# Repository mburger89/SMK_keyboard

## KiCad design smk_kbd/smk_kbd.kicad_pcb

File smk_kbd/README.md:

# Gateron LP 5×12 Wireless Keyboard — KiCad Project

59-key (5×12, bottom row 5 + 2U + 5) hot-swap low-profile keyboard, ESP32-C6 wireless, Li-ion powered with USB-C charging and a hard power switch.

Open `smk_kbd.kicad_pro` in KiCad 9. Files are in KiCad 8 format, which KiCad 9 opens natively (it will save them forward in v9 format). All symbols and footprints are embedded **and** provided as project-local libraries (`kbd.pretty`, `kbd.kicad_sym`) so nothing external is required.

## Layout

- 19.05 mm pitch, rows 0–3 are full 12-key rows.
- Row 4: 5 keys (cols 0–4) + one **2U key** centered over the two middle 1U positions (electrically column 5) + 5 keys (cols 7–11). Column 6 has no switch in row 4.
- The 2U key uses the Gateron **plate-mounted** 2U stabilizer (KS-57B210T) — it clips to the plate, so the PCB needs no stabilizer holes. Keep the area around the 2U key clear of tall components (it already is).
- Board outline 234.5 × 116.5 mm; 6 × M2 mounting holes placed in the gaps between keys.

## Switch / socket footprint

Built from the Gateron datasheets you provided:

- ø5.2 mm center hole (stem post), 2 × ø3.0 mm contact barrels at (−4.4, 4.7) and (+2.6, 5.75) from switch center, 2.55 mm square solder pads on the **back** copper — sockets mount on the back, switches insert from the front.
- Verified against the KS-2P02B01-02 drawing (7.0 mm pin spread, 1.05 mm vertical offset, 14×14 body).

## Electrical design

**Matrix** — COL2ROW: `COL → switch → diode anode → cathode → ROW`. One 1N4148W (SOD-123, back side) per key, placed left of each switch.

**GPIO map (ESP32-C6-MINI-1)**

| Function | GPIO | Module pin |
|---|---|---|
| ROW0–ROW3 (inputs) | IO0–IO3 | 12, 13, 5, 6 |
| ROW4 (input) | IO5 | 10 |
| COL0–COL11 (outputs) | IO6, IO7, IO8, IO14, IO15, IO18–IO23, IO17 | 15, 16, 22, 19, 20, 24–29, 30 |
| VBAT sense (÷2) | IO4 / ADC1_CH4 | 9 |
| USB D− / D+ | IO12 / IO13 | 17 / 18 |
| BOOT button | IO9 | 23 |
| RESET button | EN | 8 |
| Spare / UART log | TXD0 (IO16) | 31 (unconnected) |

Rows are on IO0–IO3 + IO5 deliberately: these are **LP (low-power) GPIOs**, so the firmware can use them for deep-sleep key-press wakeup, and all are ADC-capable. Note IO4/IO5/IO8/IO9/IO15 are strapping pins — harmless for a matrix (inputs at boot), just don't hold keys during reset if flashing misbehaves.

**Power**

- USB-C (HRO TYPE-C-31-M-12, 16-pin USB 2.0) with 5.1 kΩ CC pulldowns → works with C-to-C cables. ESD protection via USBLC6-2SC6.
- Charger: MCP73831-2 with 2.0 kΩ PROG = **500 mA** charge current. Use a 1000 mAh+ Li-ion cell, or raise R3 to 10 kΩ for 100 mA with smaller cells. Charge LED on STAT.
- Power path (Feather-style): VBUS → Schottky (B5819W) → VSYS; battery → DMG3415U P-FET → VSYS. When USB is plugged in, the FET gate is pulled high and the board runs from USB while the battery charges; otherwise the FET conducts from the battery.
- **Charging works with the power switch OFF** — the charger connects to the battery ahead of the switch.
- ON/OFF: the side-actuated slide switch (MSK-12C02) sits flush with the rear board edge — its lever pokes out through a case cutout next to USB. It drives the AP2112K-3.3 LDO **EN** pin between VSYS and GND — it switches microamps, not the load current, and gives a true off state (LDO Iq ≈ 55 µA off the battery when on; ~0 when off).
- Battery voltage divider 1 MΩ/1 MΩ + 100 nF into IO4 for fuel-gauge readings.
- Battery connector: JST-SH 2-pin (SM02B-SRSS-TB), surface-mount on the **back** of the board, only ~1.6 mm tall, cable exits toward the board interior. Batteries usually ship with JST-PH plugs — order one with an SH plug or re-terminate. **Check polarity against the + mark before plugging in.**

## Routing — DONE

The board is **fully routed**: matrix (columns on F.Cu, rows on B.Cu, one via
per key), MCU fanout, USB differential pair, charger, power path, LDO and
buttons — 570 track segments, 130 vias, 29 GND stitching vias. An independent
geometric check verified 0.2 mm copper clearance, 0.3 mm hole clearance,
0.3 mm edge clearance and single-component connectivity for every net.
`board_render.png` shows the routed board (red = front, blue = back).

GND is carried by the two full-board pours — fill them before export (the
export script does this automatically).

## Sending to PCBWay

1. `cd` into this folder and run the export script with KiCad's bundled Python
   (it fills the zones, saves, and writes `smk_kbd_gerbers.zip`):

   macOS: `/Applications/KiCad/KiCad.app/Contents/Frameworks/Python.framework/Versions/Current/bin/python3 export_fab.py`

   (Alternative: open the PCB in KiCad, press `B`, run DRC, then
   File → Fabrication Outputs → Gerbers + Drill Files and zip the output.)

2. Upload `smk_kbd_gerbers.zip` at pcbway.com → *Quick Order PCB*.

3. Order parameters:

   | Setting | Value |
   |---|---|
   | Board size | 234.5 × 116.5 mm |
   | Layers | 2 |
   | Thickness | **1.6 mm** |
   | Min track/spacing | 6/6 mil (design uses ≥ 0.2 mm — relaxed) |
   | Min hole | 0.3 mm |
   | Surface finish | HASL lead-free (or ENIG for nicer hot-swap pads) |
   | Copper | 1 oz |
   | Solder mask / silk | your choice |
   | Panelization | single piece |

4. Sanity checks before paying: view the Gerbers in PCBWay's online viewer or
   `gerbview` — confirm the GND pours are present on both layers (if they're
   missing you exported without filling zones) and the board outline is closed.

## PCB placement (why it routes easily)

- Socket pads are on the back; the **front layer is completely free under the matrix** — run columns vertically on F.Cu (each socket's COL pad is at the same x in a column; drop one via per key).
- Diodes are on the back, cathodes facing up — run rows horizontally on B.Cu. Row 4's 2U key is pre-assigned to column 5, so its column trace just jogs half a pitch.
- The diode anode pad sits 0.3 mm from its socket pad on the same net — join them with a stub trace.
- MCU/power strip along the top edge: battery + power mux + LDO left of the module, USB + ESD + charger right of it, BOOT/RESET buttons on the BACK of the board beside the module (press through case holes). Antenna points off the top edge with a built-in copper keepout zone (both layers) — don't route under it and keep the case plastic there.
- GND zones are defined on both layers — press `B` in pcbnew to fill.

## BOM (besides 59 switches, 59 sockets, keycaps, 2U plate stab)

| Ref | Part | Package |
|---|---|---|
| U1 | ESP32-C6-MINI-1 | SMD module |
| U2 | MCP73831-2ACI/OT | SOT-23-5 |
| U3 | AP2112K-3.3TRG1 | SOT-23-5 |
| U4 | USBLC6-2SC6 | SOT-23-6 |
| Q1 | DMG3415U (P-MOSFET) | SOT-23 |
| D1–D59 | 1N4148W | SOD-123 |
| D60 | B5819W / SS14 Schottky | SOD-123 |
| LED1 | LED (charge) | 0603 |
| J1 | HRO TYPE-C-31-M-12 (LCSC C165948) | SMD |
| J2 | JST SH **SM02B-SRSS-TB** (1.0 mm, low-profile side entry, on the **back**) | SMD |
| SW60/61 | 6×6 mm tactile (mounted on the **back** side) | THT |
| SW62 | MSK-12C02 side-actuated slide SPDT, lever exits rear edge | SMD |
| R1,R2 | 5.1 kΩ | 0603 |
| R3 | 2.0 kΩ | 0603 |
| R4 | 1 kΩ | 0603 |
| R5 | 100 kΩ | 0603 |
| R6,R7 | 1 MΩ | 0603 |
| R8 | 10 kΩ | 0603 |
| C1,C2 | 4.7 µF | 0603 |
| C3,C6 | 1 µF | 0603 |
| C4,C7 | 10 µF | 0603 |
| C5,C8 | 100 nF | 0603 |

## 3D models

Every footprint carries a 3D model, so KiCad's 3D viewer (`Alt+3`) shows the
assembled board:

- Switches: your `Gateron_KS-33.step` (in `3dmodels/`), one per key, plus a
  generated hot-swap socket model on the back side.
- ESP32-C6-MINI-1 and the MSK-12C02 slide switch: generated models in
  `3dmodels/` (dimensionally correct simplified shapes).
- Everything else (SOT-23s, 0603 R/C/LED, SOD-123 diodes, HRO USB-C, JST-PH,
  6 mm buttons) references KiCad 9's stock library via `${KICAD9_3DMODEL_DIR}`.
  If a part renders blank, install the "3D models" package from the KiCad
  installer — the references resolve automatically.

If the switch model appears rotated (LED window on the wrong side), edit one
footprint's model rotation and use Edit → "Change Footprints" to apply to all.

## Firmware notes

ZMK (with the ESP32 port) or ESP-IDF/Arduino work; the C6 supports BLE 5 + 802.15.4. Matrix: COL2ROW, diode direction col→row. Native USB (IO12/13) gives flashing and serial with no UART bridge; hold BOOT while tapping RESET for download mode.

## Final checks before ordering

1. Run `export_fab.py` (fills zones + saves), or open the PCB, press `B`, save.
2. Run KiCad's own DRC once for confidence — the design was verified by an independent geometric checker, but a second opinion is free.
3. Verify the slide-switch footprint against the exact part you buy (MSK-12C02 clones vary slightly).
4. The HRO USB-C legs are officially specced for thinner boards — they solder fine on 1.6 mm (standard practice on keyboards), or swap in a GCT USB4105 footprint if you prefer.

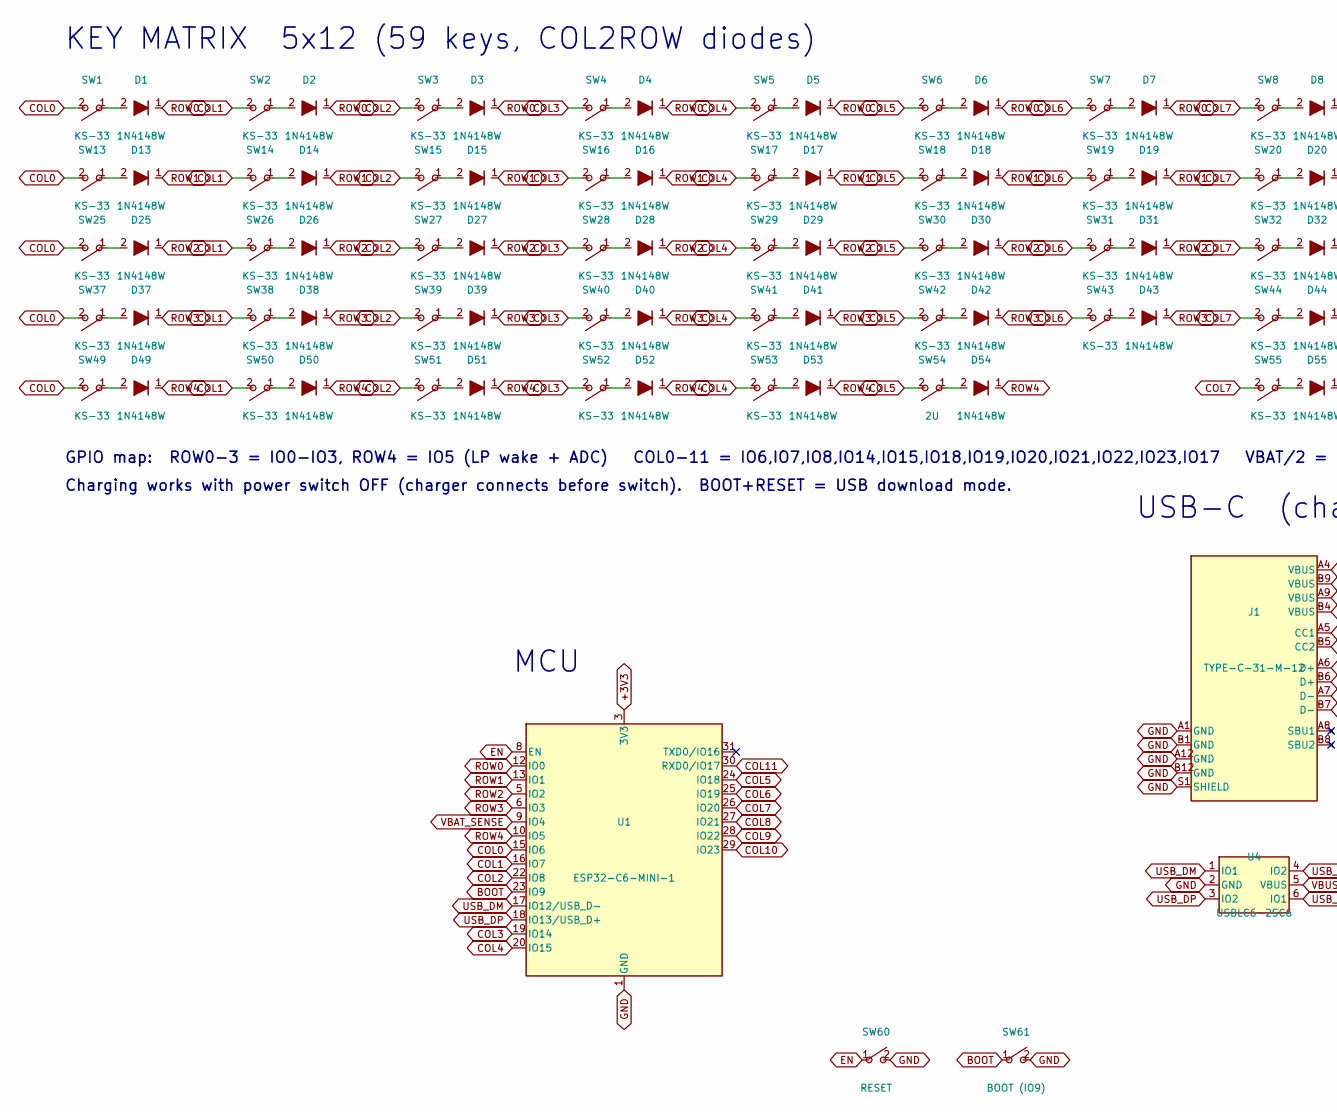
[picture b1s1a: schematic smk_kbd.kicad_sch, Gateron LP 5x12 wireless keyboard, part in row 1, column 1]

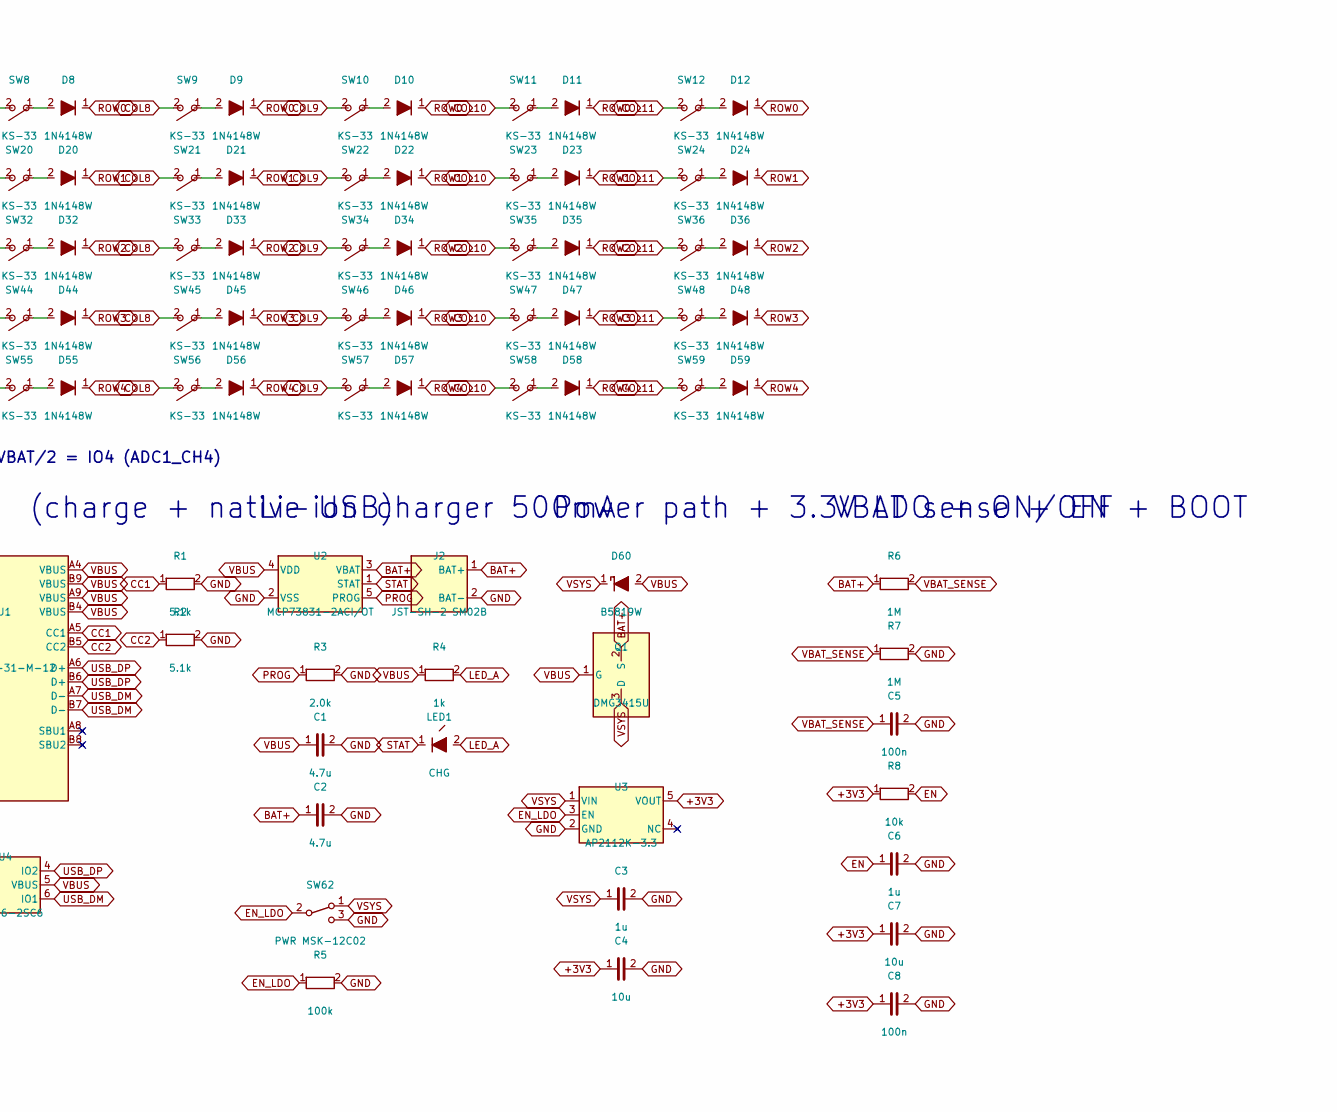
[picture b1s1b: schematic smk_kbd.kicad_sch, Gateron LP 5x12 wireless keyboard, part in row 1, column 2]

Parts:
C1, C2: 4.7u; RC_0603
C3, C6: 1u; RC_0603
C4, C7: 10u; RC_0603
C5, C8: 100n; RC_0603
D1, D2, D3, D4, D5, D6, D7, D8, D9, D10, D11, D12, D13, D14, D15, D16, D17, D18, D19, D20, D21, D22, D23, D24, D25, D26, D27, D28, D29, D30, D31, D32, D33, D34, D35, D36, D37, D38, D39, D40, D41, D42, D43, D44, D45, D46, D47, D48, D49, D50, D51, D52, D53, D54, D55, D56, D57, D58, D59: 1N4148W; D_SOD-123_Back
D60: B5819W; D_SOD-123_Back
J1: TYPE-C-31-M-12; USB_C_Receptacle_HRO_TYPE-C-31-M-12
J2: JST-SH-2 SM02B; JST_SH_SM02B_2pin_Back
LED1: CHG; LED_0603
Q1: DMG3415U; SOT-23
R1, R2: 5.1k; RC_0603
R3: 2.0k; RC_0603
R4: 1k; RC_0603
R5: 100k; RC_0603
R6, R7: 1M; RC_0603
R8: 10k; RC_0603
SW1, SW2, SW3, SW4, SW5, SW6, SW7, SW8, SW9, SW10, SW11, SW12, SW13, SW14, SW15, SW16, SW17, SW18, SW19, SW20, SW21, SW22, SW23, SW24, SW25, SW26, SW27, SW28, SW29, SW30, SW31, SW32, SW33, SW34, SW35, SW36, SW37, SW38, SW39, SW40, SW41, SW42, SW43, SW44, SW45, SW46, SW47, SW48, SW49, SW50, SW51, SW52, SW53, SW55, SW56, SW57, SW58, SW59: KS-33; SW_Gateron_KS33_HS
SW54: 2U; SW_Gateron_KS33_HS
SW60: RESET; SW_PUSH_6mm_THT
SW61: BOOT (IO9); SW_PUSH_6mm_THT
SW62: PWR MSK-12C02; SW_Slide_MSK12C02
U1: ESP32-C6-MINI-1
U2: MCP73831-2ACI/OT; SOT-23-5
U3: AP2112K-3.3; SOT-23-5
U4: USBLC6-2SC6; SOT-23-6

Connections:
+3V3: C4.1, C7.1, C8.1, R8.1, U1.3 (3V3), U3.5 (VOUT)
BAT+: C2.1, J2.1 (BAT+), Q1.2 (S), R6.1, U2.3 (VBAT)
BOOT: SW61.1, U1.23 (IO9)
CC1: J1.A5 (CC1), R1.1
CC2: J1.B5 (CC2), R2.1
COL0: SW1.2, SW13.2, SW25.2, SW37.2, SW49.2, U1.15 (IO6)
COL1: SW2.2, SW14.2, SW26.2, SW38.2, SW50.2, U1.16 (IO7)
COL2: SW3.2, SW15.2, SW27.2, SW39.2, SW51.2, U1.22 (IO8)
COL3: SW4.2, SW16.2, SW28.2, SW40.2, SW52.2, U1.19 (IO14)
COL4: SW5.2, SW17.2, SW29.2, SW41.2, SW53.2, U1.20 (IO15)
COL5: SW6.2, SW18.2, SW30.2, SW42.2, SW54.2, U1.24 (IO18)
COL6: SW7.2, SW19.2, SW31.2, SW43.2, U1.25 (IO19)
COL7: SW8.2, SW20.2, SW32.2, SW44.2, SW55.2, U1.26 (IO20)
COL8: SW9.2, SW21.2, SW33.2, SW45.2, SW56.2, U1.27 (IO21)
COL9: SW10.2, SW22.2, SW34.2, SW46.2, SW57.2, U1.28 (IO22)
COL10: SW11.2, SW23.2, SW35.2, SW47.2, SW58.2, U1.29 (IO23)
COL11: SW12.2, SW24.2, SW36.2, SW48.2, SW59.2, U1.30 (RXD0/IO17)
EN: C6.1, R8.2, SW60.1, U1.8 (EN)
EN_LDO: R5.1, SW62.2 (C), U3.3 (EN)
GND: C1.2, C2.2, C3.2, C4.2, C5.2, C6.2, C7.2, C8.2, J1.A1 (GND), J1.A12 (GND), J1.B1 (GND), J1.B12 (GND), J1.S1 (SHIELD), J2.2 (BAT-), R1.2, R2.2, R3.2, R5.2, R7.2, SW60.2, SW61.2, SW62.3 (B), U1.1 (GND), U1.2 (GND), U1.11 (GND), U1.14 (GND), U1.36 (GND), U1.37 (GND), U1.38 (GND), U1.39 (GND), U1.40 (GND), U1.41 (GND), U1.42 (GND), U1.43 (GND), U1.44 (GND), U1.45 (GND), U1.46 (GND), U1.47 (GND), U1.48 (GND), U1.49 (GND), U1.50 (GND), U1.51 (GND), U1.52 (GND), U1.53 (GND), U2.2 (VSS), U3.2 (GND), U4.2 (GND)
LED_A: LED1.2, R4.2
N_R0C0: D1.2, SW1.1
N_R0C1: D2.2, SW2.1
N_R0C2: D3.2, SW3.1
N_R0C3: D4.2, SW4.1
N_R0C4: D5.2, SW5.1
N_R0C5: D6.2, SW6.1
N_R0C6: D7.2, SW7.1
N_R0C7: D8.2, SW8.1
N_R0C8: D9.2, SW9.1
N_R0C9: D10.2, SW10.1
N_R0C10: D11.2, SW11.1
N_R0C11: D12.2, SW12.1
N_R1C0: D13.2, SW13.1
N_R1C1: D14.2, SW14.1
N_R1C2: D15.2, SW15.1
N_R1C3: D16.2, SW16.1
N_R1C4: D17.2, SW17.1
N_R1C5: D18.2, SW18.1
N_R1C6: D19.2, SW19.1
N_R1C7: D20.2, SW20.1
N_R1C8: D21.2, SW21.1
N_R1C9: D22.2, SW22.1
N_R1C10: D23.2, SW23.1
N_R1C11: D24.2, SW24.1
N_R2C0: D25.2, SW25.1
N_R2C1: D26.2, SW26.1
N_R2C2: D27.2, SW27.1
N_R2C3: D28.2, SW28.1
N_R2C4: D29.2, SW29.1
N_R2C5: D30.2, SW30.1
N_R2C6: D31.2, SW31.1
N_R2C7: D32.2, SW32.1
N_R2C8: D33.2, SW33.1
N_R2C9: D34.2, SW34.1
N_R2C10: D35.2, SW35.1
N_R2C11: D36.2, SW36.1
N_R3C0: D37.2, SW37.1
N_R3C1: D38.2, SW38.1
N_R3C2: D39.2, SW39.1
N_R3C3: D40.2, SW40.1
N_R3C4: D41.2, SW41.1
N_R3C5: D42.2, SW42.1
N_R3C6: D43.2, SW43.1
N_R3C7: D44.2, SW44.1
N_R3C8: D45.2, SW45.1
N_R3C9: D46.2, SW46.1
N_R3C10: D47.2, SW47.1
N_R3C11: D48.2, SW48.1
N_R4C0: D49.2, SW49.1
N_R4C1: D50.2, SW50.1
N_R4C2: D51.2, SW51.1
N_R4C3: D52.2, SW52.1
N_R4C4: D53.2, SW53.1
N_R4C5: D54.2, SW54.1
N_R4C7: D55.2, SW55.1
N_R4C8: D56.2, SW56.1
N_R4C9: D57.2, SW57.1
N_R4C10: D58.2, SW58.1
N_R4C11: D59.2, SW59.1
PROG: R3.1, U2.5 (PROG)
ROW0: D1.1, D2.1, D3.1, D4.1, D5.1, D6.1, D7.1, D8.1, D9.1, D10.1, D11.1, D12.1, U1.12 (IO0)
ROW1: D13.1, D14.1, D15.1, D16.1, D17.1, D18.1, D19.1, D20.1, D21.1, D22.1, D23.1, D24.1, U1.13 (IO1)
ROW2: D25.1, D26.1, D27.1, D28.1, D29.1, D30.1, D31.1, D32.1, D33.1, D34.1, D35.1, D36.1, U1.5 (IO2)
ROW3: D37.1, D38.1, D39.1, D40.1, D41.1, D42.1, D43.1, D44.1, D45.1, D46.1, D47.1, D48.1, U1.6 (IO3)
ROW4: D49.1, D50.1, D51.1, D52.1, D53.1, D54.1, D55.1, D56.1, D57.1, D58.1, D59.1, U1.10 (IO5)
STAT: LED1.1, U2.1 (STAT)
USB_DM: J1.A7 (D-), J1.B7 (D-), U1.17 (IO12/USB_D-), U4.1 (IO1), U4.6 (IO1)
USB_DP: J1.A6 (D+), J1.B6 (D+), U1.18 (IO13/USB_D+), U4.3 (IO2), U4.4 (IO2)
VBAT_SENSE: C5.1, R6.2, R7.1, U1.9 (IO4)
VBUS: C1.1, D60.2, J1.A4 (VBUS), J1.A9 (VBUS), J1.B4 (VBUS), J1.B9 (VBUS), Q1.1 (G), R4.1, U2.4 (VDD), U4.5 (VBUS)
VSYS: C3.1, D60.1, Q1.3 (D), SW62.1 (A), U3.1 (VIN)

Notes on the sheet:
KEY MATRIX 5x12 (59 keys, COL2ROW diodes)
MCU
USB-C (charge + native USB)
Li-ion charger 500mA
Power path + 3.3V LDO + ON/OFF
VBAT sense + EN + BOOT
GPIO map: ROW0-3 = IO0-IO3, ROW4 = IO5 (LP wake + ADC) COL0-11 = IO6,IO7,IO8,IO14,IO15,IO18,IO19,IO20,IO21,IO22,IO23,IO17 VBAT/2 = IO4 (ADC1_CH4)
Charging works with power switch OFF (charger connects before switch). BOOT+RESET = USB download mode.

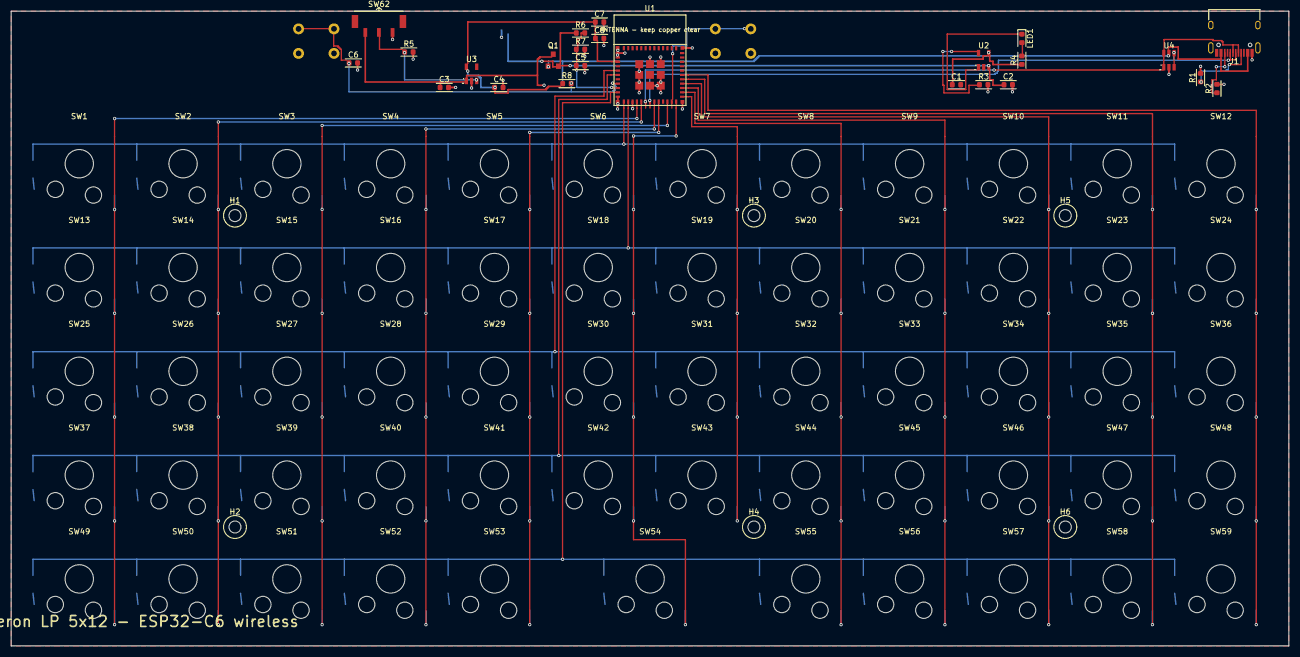
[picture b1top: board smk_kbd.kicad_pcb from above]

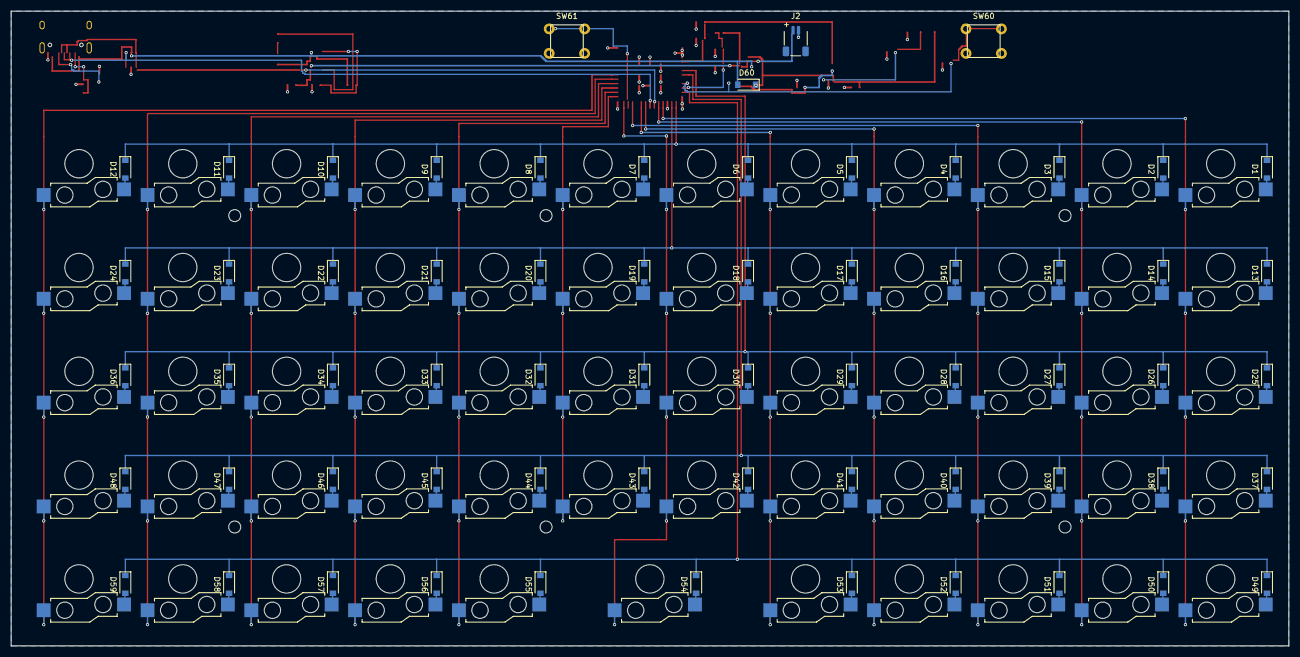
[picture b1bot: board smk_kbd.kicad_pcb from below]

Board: 2 copper layers, 234.5 x 116.5 mm, 152 parts (63 on the bottom side), 92 nets.

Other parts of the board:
H1, H2, H3, H4, H5, H6: M2; MountingHole_M2

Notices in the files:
generate_kbd_rp2040.py:
comments repeatedly cite as blocking the U1-north escape pocket
